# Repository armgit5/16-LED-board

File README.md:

# 16-LED-board

2 layers 16 LED with shift register board designed in KiCad.

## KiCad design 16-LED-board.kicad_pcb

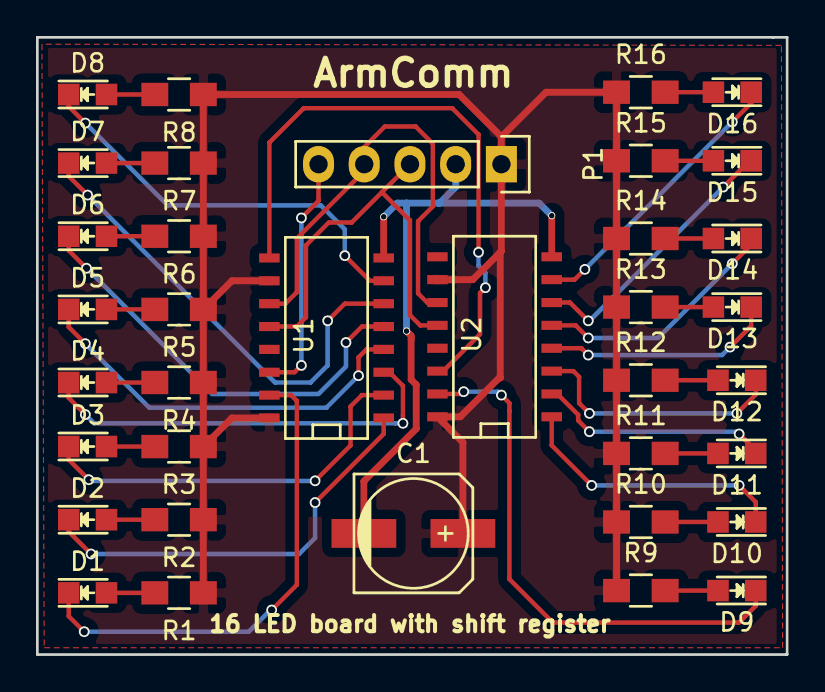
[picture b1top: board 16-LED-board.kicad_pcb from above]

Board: 2 copper layers, 41.7 x 34.3 mm, 36 parts (0 on the bottom side), 38 nets.

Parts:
C1: 200uF; c_elec_6.3x5.3
D1, D2, D3, D4, D5, D6, D7, D8, D9, D10, D11, D12, D13, D14, D15, D16: LED; LED_0805
P1: CONN_01X05; Pin_Header_Straight_1x05
R1, R2, R3, R4, R5, R6, R7, R8, R9, R10, R11, R12, R13, R14, R15, R16: 220Ohm; R_0805_HandSoldering
U1, U2: 74HC595; SO-16-N

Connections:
/CLOCK: P1.4, U1.11, U2.11
/DATA: P1.5, U1.14
/DATA_S: U1.9, U2.14
/LATCH: P1.3, U1.12, U2.12
/led_1_1: D1.1, U1.15
/led_1_2: D2.1, U1.1
/led_1_3: D3.1, U1.2
/led_1_4: D4.1, U1.3
/led_1_5: D5.1, U1.4
/led_1_6: D6.1, U1.5
/led_1_7: D7.1, U1.6
/led_1_8: D8.1, U1.7
/led_2_1: D9.1, U2.15
/led_2_2: D10.1, U2.1
/led_2_3: D11.1, U2.2
/led_2_4: D12.1, U2.3
/led_2_5: D13.1, U2.4
/led_2_6: D14.1, U2.5
/led_2_7: D15.1, U2.6
/led_2_8: D16.1, U2.7
GND: C1.2, P1.2, U1.8, U2.8
unnamed: D1.2, R1.2
unnamed: D2.2, R2.2
unnamed: D3.2, R3.2
unnamed: D4.2, R4.2
unnamed: D5.2, R5.2
unnamed: D6.2, R6.2
unnamed: D7.2, R7.2
unnamed: D8.2, R8.2
unnamed: D9.2, R9.2
unnamed: D10.2, R10.2
unnamed: D11.2, R11.2
unnamed: D12.2, R12.2
unnamed: D13.2, R13.2
unnamed: D14.2, R14.2
unnamed: D15.2, R15.2
unnamed: D16.2, R16.2
VCC: C1.1, P1.1, R1.1, R2.1, R3.1, R4.1, R5.1, R6.1, R7.1, R8.1, R9.1, R10.1, R11.1, R12.1, R13.1, R14.1, R15.1, R16.1, U1.10, U1.16, U2.10, U2.16
